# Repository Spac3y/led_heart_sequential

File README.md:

# LED Heart Sequential

This circuit drives a sequential LED display (arranged in a heart shape) using a NE555 timer in astable mode paired with a CD4017 decade counter.
### NE555 – Astable Oscillator
The NA555P is configured in astable mode, generating a continuous square wave clock signal. In this mode, the output continuously toggles between HIGH and LOW with no stable state, requiring no external trigger.
The timing network consists of:

- R1 (1kΩ) — charge resistor (between VCC and DISCH)
- R2 — discharge resistor (between DISCH and TRIG/THRES)
- C1 (100µF) — timing capacitor

The capacitor charges through R1 + R2 and discharges through R2 only, which sets the frequency and duty cycle:

```math
 f = 1.44 / (R_1 + 2R_2)*C_1

 D = R_1 + R_2 / R_1 + 2R_2 * 100%

```

The output (pin 3) feeds directly into the CLK pin (pin 14) of the CD4017.

### CD4017 – Decade Counter / Sequencer
The CD4017 is a Johnson decade counter with 10 decoded outputs (Q0–Q9). On each rising edge of the clock signal received from the 555, it activates the next output in sequence — only one output is HIGH at any given time.

CKEN (pin 13) is tied LOW → counter is always enabled
Reset (pin 15) is tied LOW → the counter cycles freely from Q0 back to Q0 after Q9
Cout (pin 12) is left unconnected (marked with ×)

Each output Q0–Q9 drives two LEDs in parallel through individual 220Ω current-limiting resistors (R3–R22), for a total of 20 LEDs (D1–D20).
### Overall Effect
The result is a chasing / sequential light animation: LEDs light up two at a time in order, cycling continuously around the heart shape. The speed of the animation is set by the 555 oscillator frequency — adjusting R2 speeds up or slows down the chase effect.
Power is supplied at +3.3V and the circuit can be enabled/disabled via SW1

## Main Components
- NE555 timer
- CD4017BE

## Repository Structure
- `project.kicad_sch` — schematic
- `project.kicad_pcb` — PCB layout
- `gerbers/` — production files
- `bom.csv` — bill of materials

## Requirements
- KiCad 9.0.7

## Status
Work in progress

# Schematic

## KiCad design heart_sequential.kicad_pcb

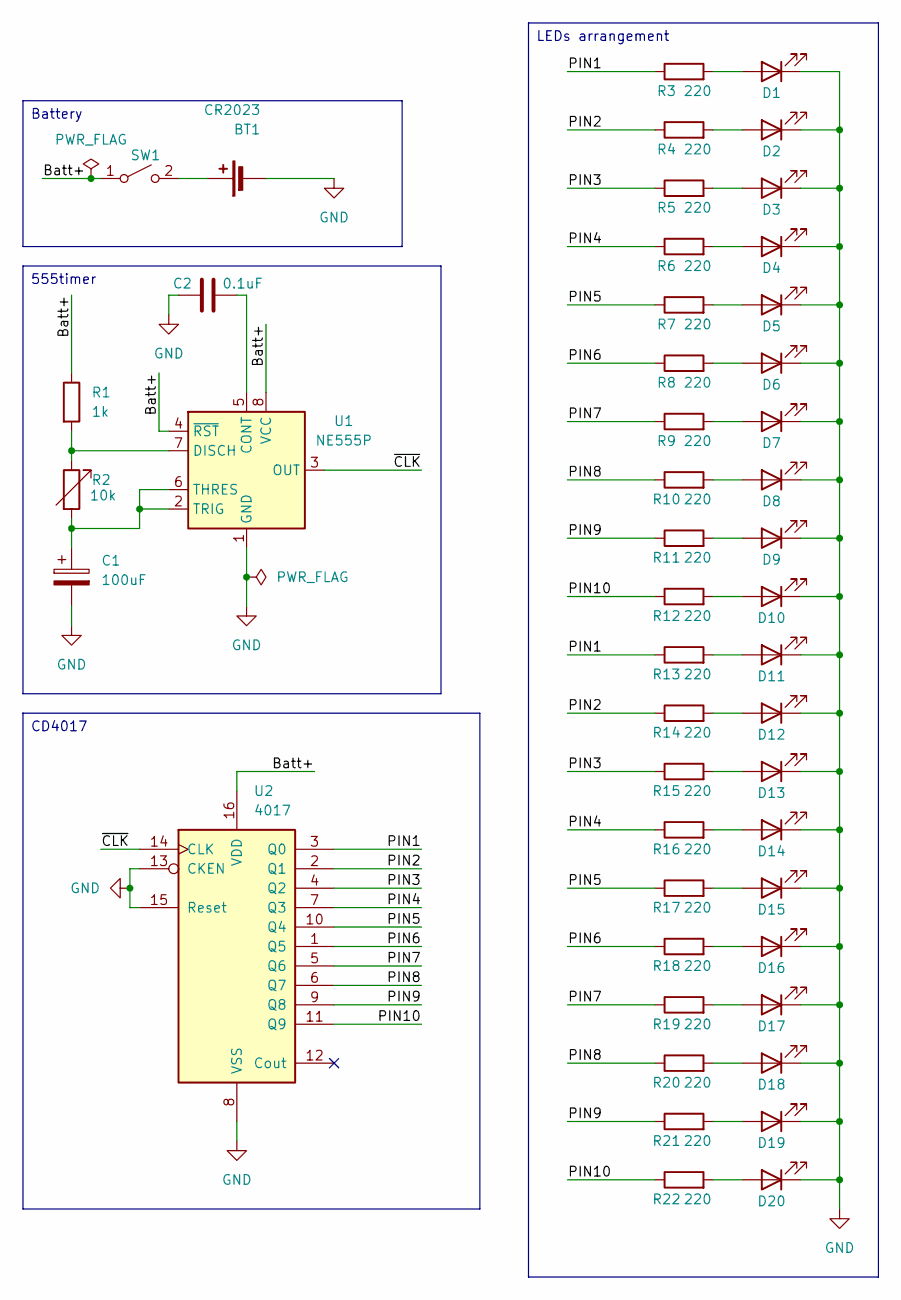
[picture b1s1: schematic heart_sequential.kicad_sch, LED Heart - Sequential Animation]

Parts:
BT1: CR2023; BatteryHolder_Keystone_2479_3xAAA
C1: 100uF; CP_Radial_D5.0mm_P2.50mm
C2: 0.1uF; C_Disc_D5.0mm_W2.5mm_P2.50mm
D1, D2, D3, D4, D5, D6, D7, D8, D9, D10, D11, D12, D13, D14, D15, D16, D17, D18, D19, D20: LED; LED_D5.0mm
R1: 1k; R_Axial_DIN0411_L9.9mm_D3.6mm_P12.70mm_Horizontal
R2: 10k; Potentiometer_Bourns_3266Y_Vertical
R3, R4, R5, R6, R7, R8, R9, R10, R11, R12, R13, R14, R15, R16, R17, R18, R19, R20, R21, R22: 220; R_Axial_DIN0411_L9.9mm_D3.6mm_P12.70mm_Horizontal
SW1: SW_SPST; SW_Slide_SPDT_Straight_CK_OS102011MS2Q
U1: NE555P; DIP-8_W7.62mm
U2: 4017; cd4017be

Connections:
/Batt+: R1.1, SW1.1 (A), U1.4 (~RST), U1.8 (VCC), U2.16 (VDD)
/PIN1: R3.1, R13.1, U2.3 (Q0)
/PIN2: R4.1, R14.1, U2.2 (Q1)
/PIN3: R5.1, R15.1, U2.4 (Q2)
/PIN4: R6.1, R16.1, U2.7 (Q3)
/PIN5: R7.1, R17.1, U2.10 (Q4)
/PIN6: R8.1, R18.1, U2.1 (Q5)
/PIN7: R9.1, R19.1, U2.5 (Q6)
/PIN8: R10.1, R20.1, U2.6 (Q7)
/PIN9: R11.1, R21.1, U2.9 (Q8)
/PIN10: R12.1, R22.1, U2.11 (Q9)
/~CLK: U1.3 (OUT), U2.14 (CLK)
GND: BT1.2 (-), C1.2, C2.1, D1.1 (K), D2.1 (K), D3.1 (K), D4.1 (K), D5.1 (K), D6.1 (K), D7.1 (K), D8.1 (K), D9.1 (K), D10.1 (K), D11.1 (K), D12.1 (K), D13.1 (K), D14.1 (K), D15.1 (K), D16.1 (K), D17.1 (K), D18.1 (K), D19.1 (K), D20.1 (K), U1.1 (GND), U2.8 (VSS), U2.13 (CKEN), U2.15 (Reset)
unnamed: BT1.1 (+), SW1.2 (B)
unnamed: D1.2 (A), R3.2
unnamed: D2.2 (A), R4.2
unnamed: D3.2 (A), R5.2
unnamed: D4.2 (A), R6.2
unnamed: D5.2 (A), R7.2
unnamed: D6.2 (A), R8.2
unnamed: D7.2 (A), R9.2
unnamed: D8.2 (A), R10.2
unnamed: D9.2 (A), R11.2
unnamed: D10.2 (A), R12.2
unnamed: D11.2 (A), R13.2
unnamed: D12.2 (A), R14.2
unnamed: D13.2 (A), R15.2
unnamed: D14.2 (A), R16.2
unnamed: D15.2 (A), R17.2
unnamed: D16.2 (A), R18.2
unnamed: D17.2 (A), R19.2
unnamed: D18.2 (A), R20.2
unnamed: D19.2 (A), R21.2
unnamed: D20.2 (A), R22.2
unnamed: C2.2, U1.5 (CONT)
unnamed: R1.2, R2.1, U1.7 (DISCH)
unnamed: C1.1, R2.2, U1.2 (TRIG), U1.6 (THRES)

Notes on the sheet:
555timer
LEDs arrangement
CD4017
Battery

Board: 2 copper layers, 48 parts (1 on the bottom side), 37 nets, no tracks yet.

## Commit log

2026-04-06 Add KiCad project for LED heart sequential
    Initial import of the KiCad project for "LED Heart - Sequential Animation": adds schematic (heart_sequential.kicad_sch), PCB and project files (heart_sequential.kicad_pcb, .kicad_prl, .kicad_pro), RE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
2026-04-16 Update schematic
